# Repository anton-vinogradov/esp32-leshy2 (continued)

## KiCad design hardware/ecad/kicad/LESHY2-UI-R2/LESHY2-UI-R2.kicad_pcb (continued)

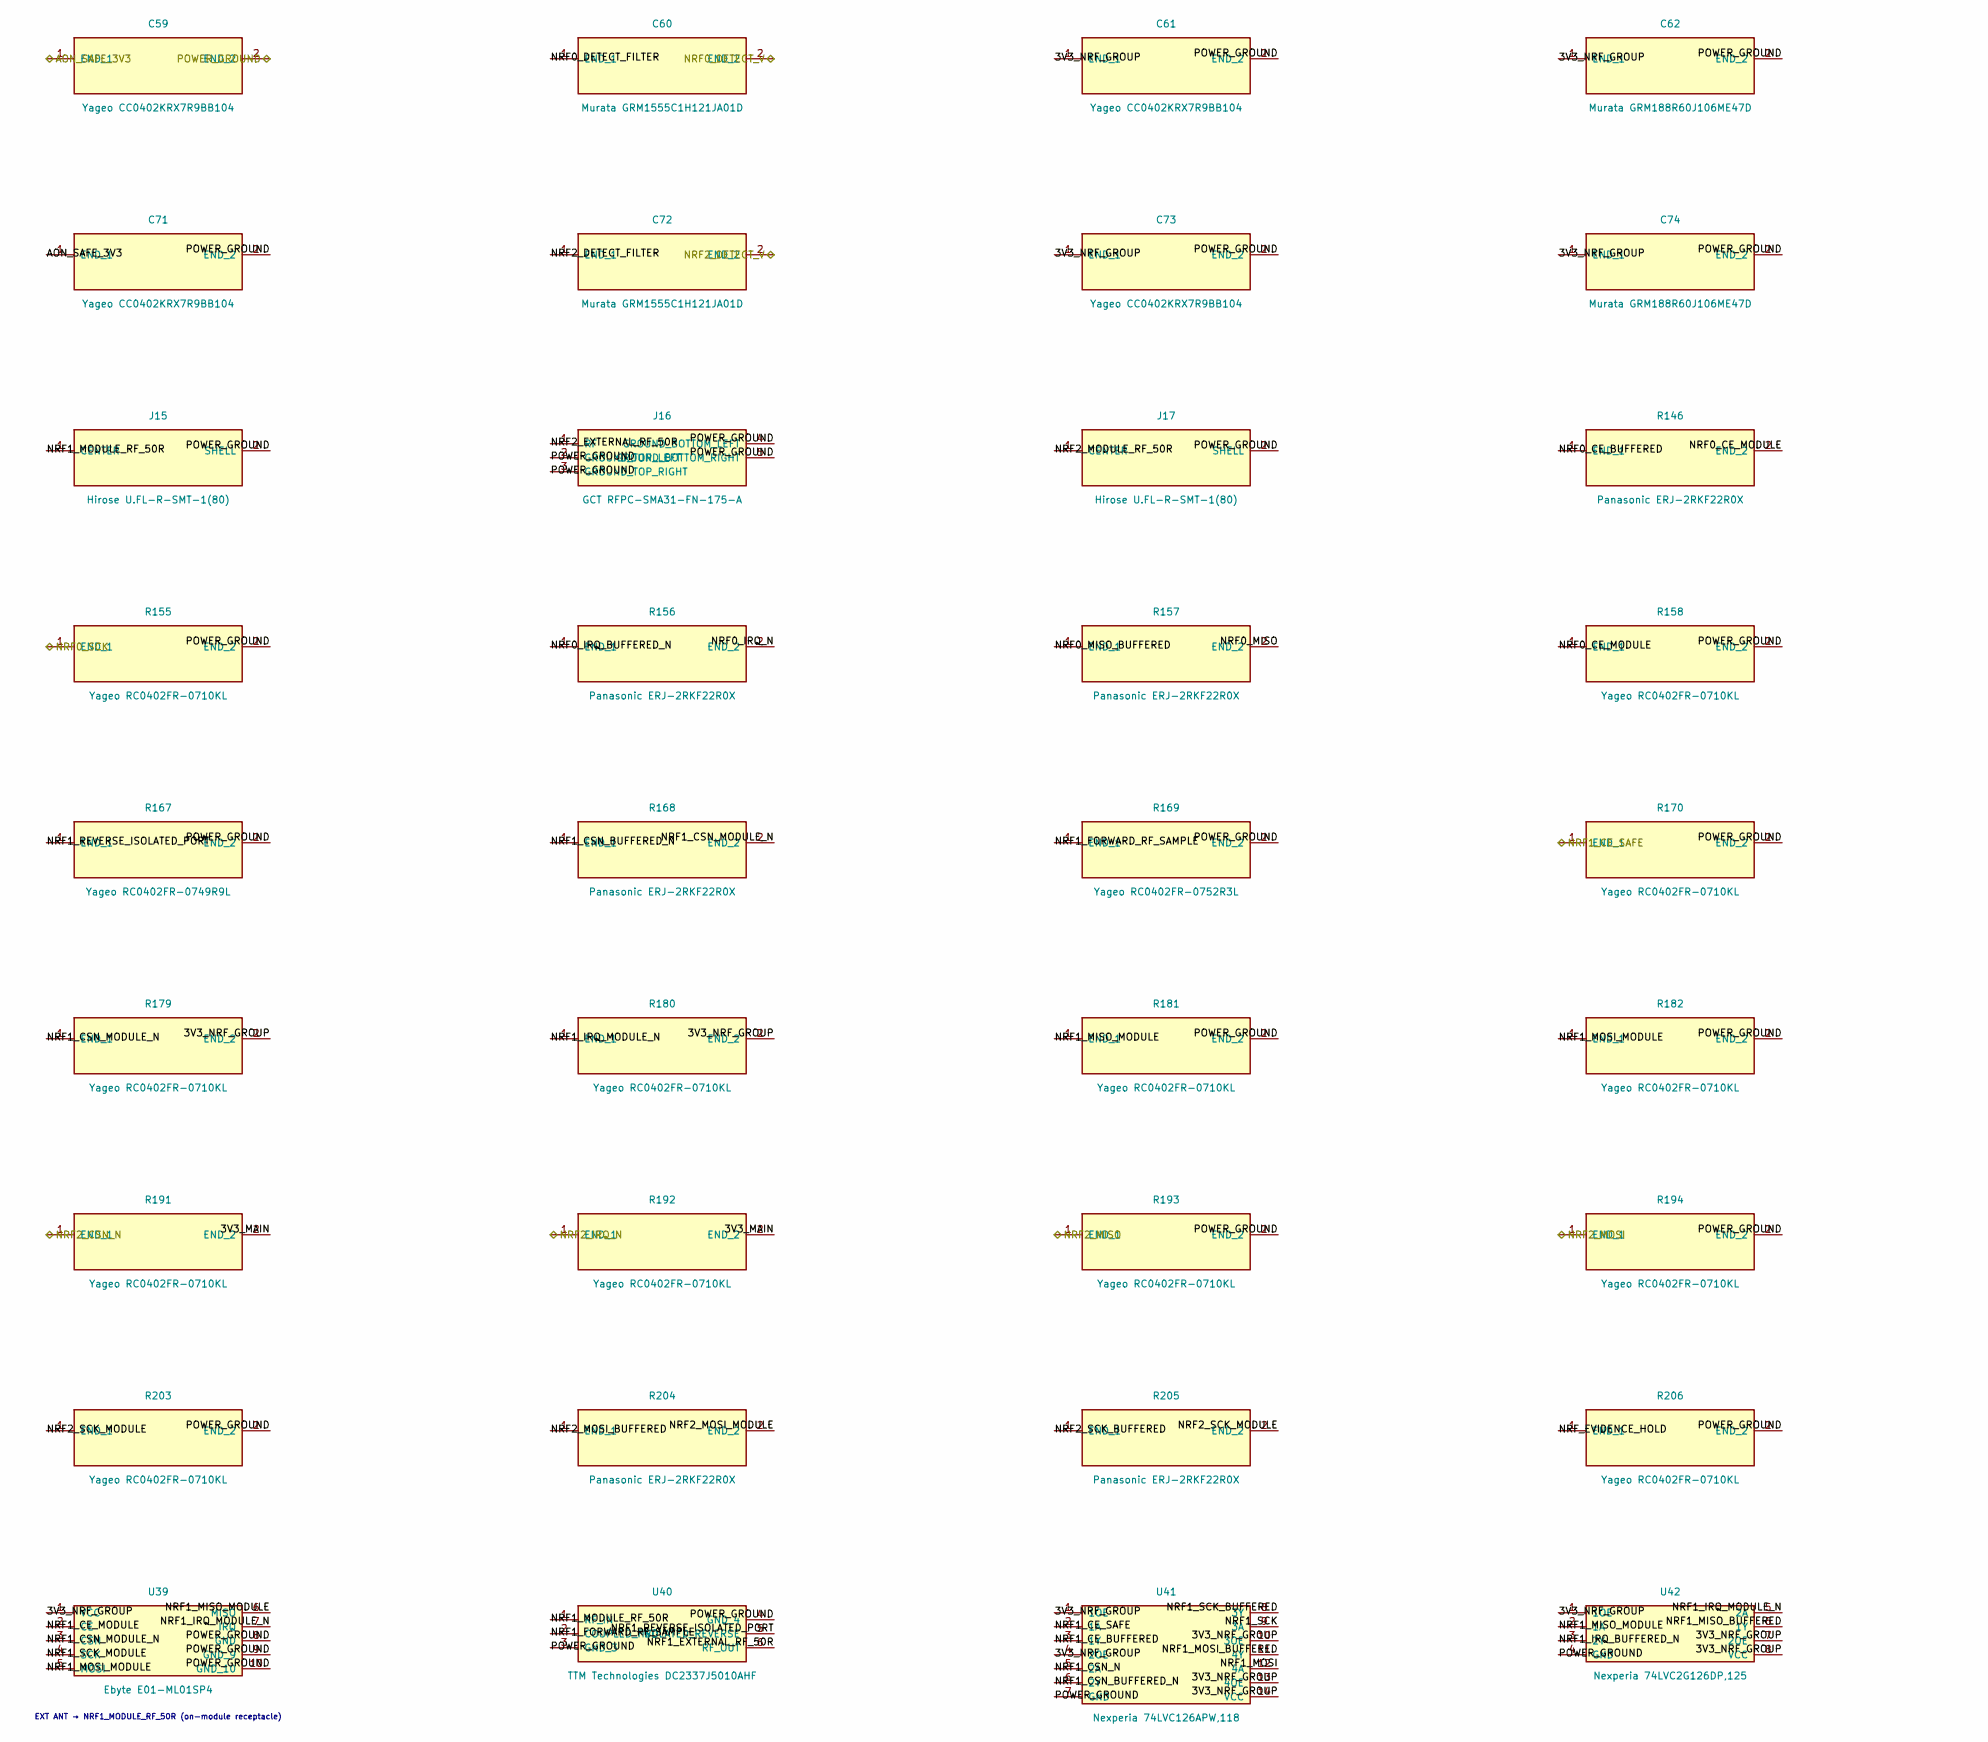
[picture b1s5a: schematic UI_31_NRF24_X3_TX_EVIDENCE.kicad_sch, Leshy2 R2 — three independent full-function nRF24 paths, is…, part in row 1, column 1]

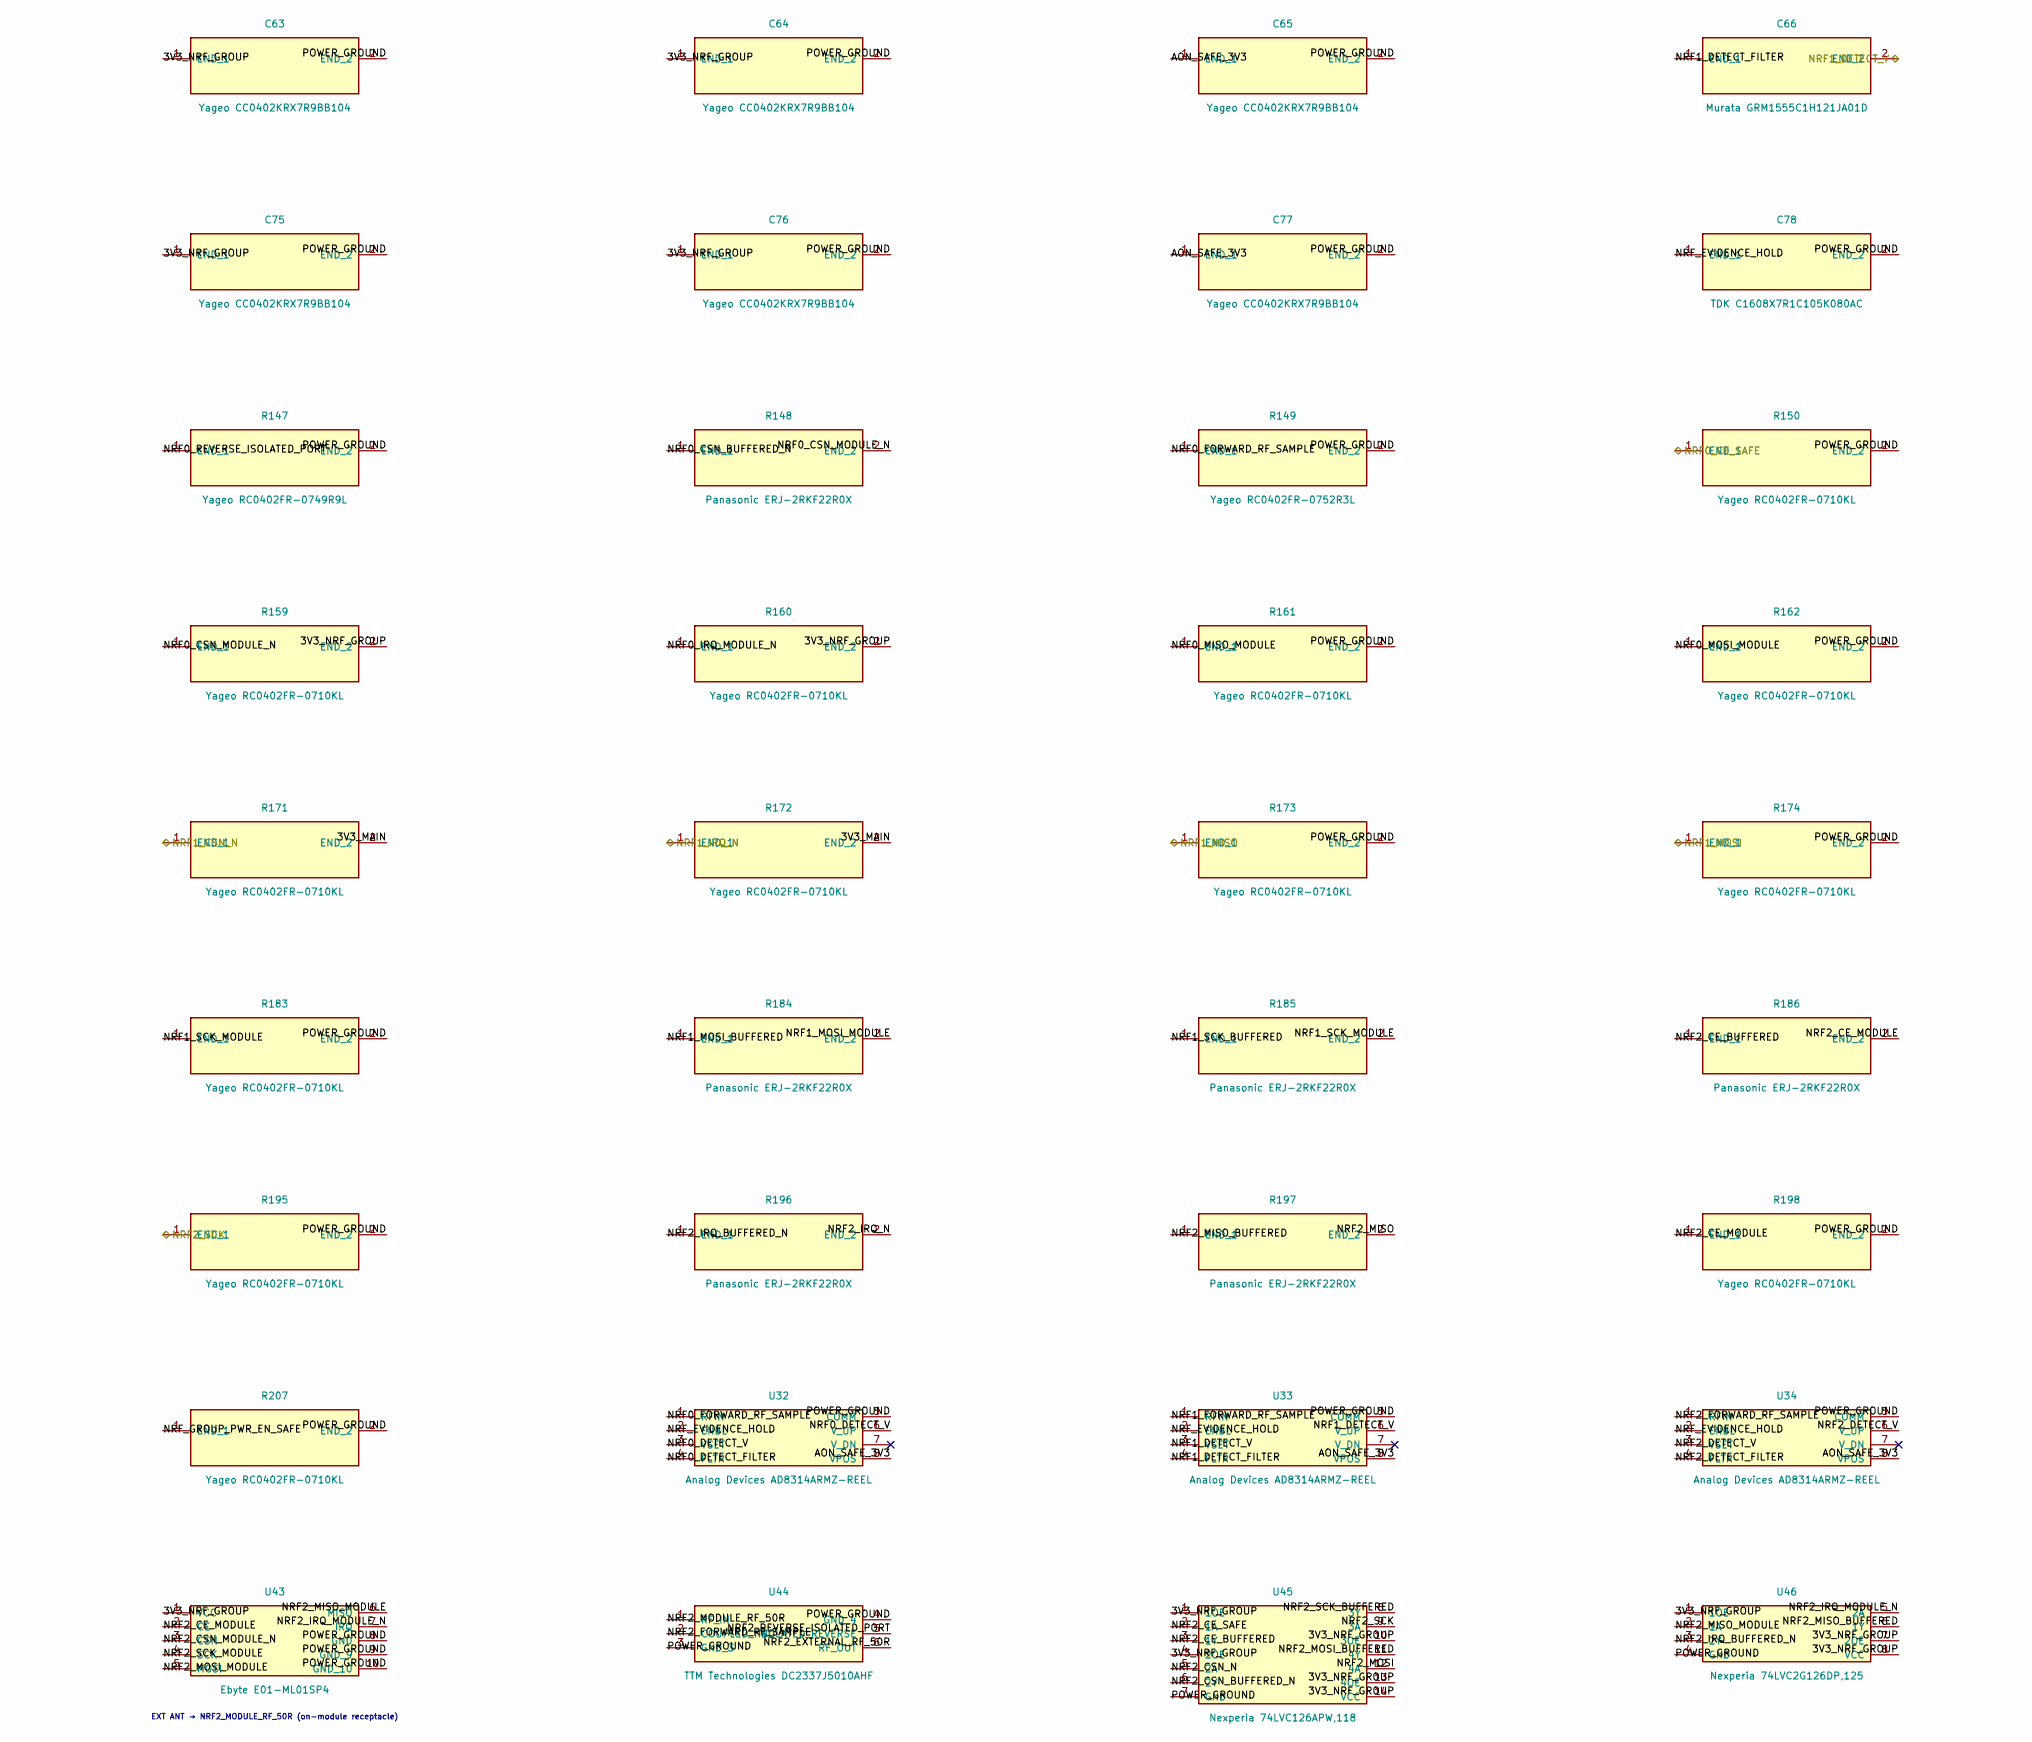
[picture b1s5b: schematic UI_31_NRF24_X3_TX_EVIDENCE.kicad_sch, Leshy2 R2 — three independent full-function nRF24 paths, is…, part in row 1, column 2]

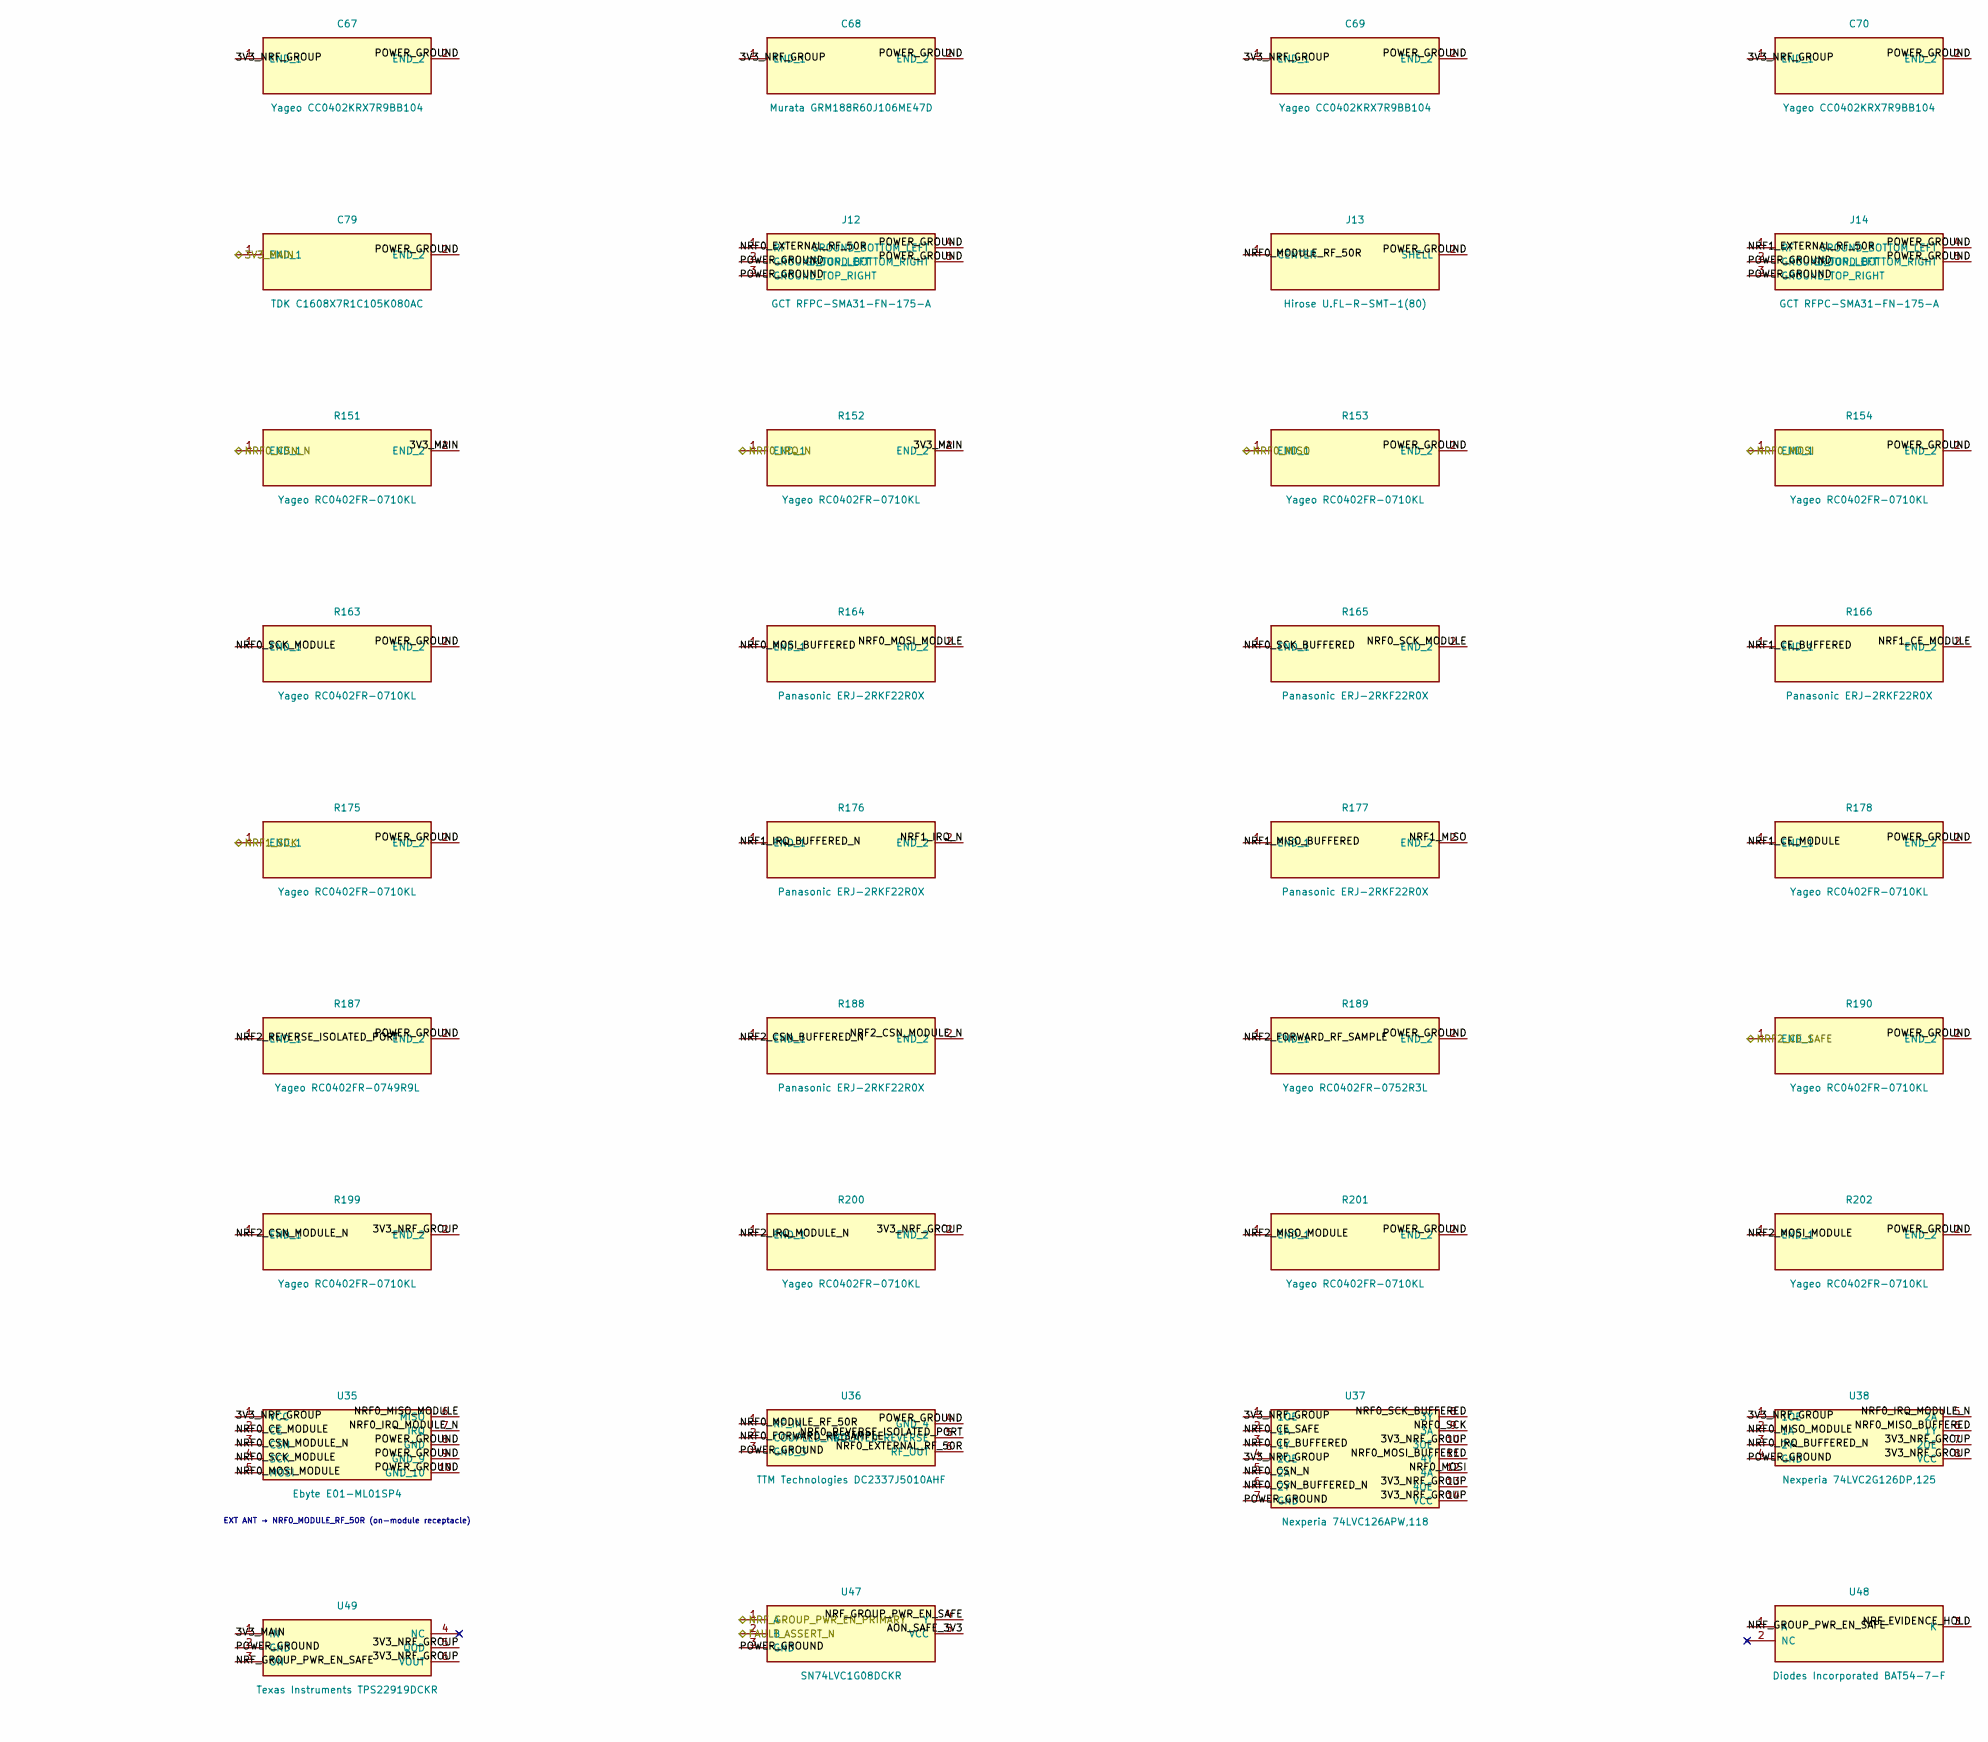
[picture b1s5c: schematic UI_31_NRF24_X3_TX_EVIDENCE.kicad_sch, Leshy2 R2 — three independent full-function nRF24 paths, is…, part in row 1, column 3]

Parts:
C59, C61, C63, C64, C65, C67, C69, C70, C71, C73, C75, C76, C77: Yageo CC0402KRX7R9BB104; C_0402_1005Metric
C60, C66, C72: Murata GRM1555C1H121JA01D; C_0402_1005Metric
C62, C68, C74: Murata GRM188R60J106ME47D; C_0603_1608Metric
C78, C79: TDK C1608X7R1C105K080AC; C_0603_1608Metric
J12, J14, J16: GCT RFPC-SMA31-FN-175-A; RFPC-SMA31-FN-175-A
J13, J15, J17: Hirose U.FL-R-SMT-1(80); U.FL_Hirose_U.FL-R-SMT-1_Vertical
R146, R148, R156, R157, R164, R165, R166, R168, R176, R177, R184, R185, R186, R188, R196, R197, R204, R205: Panasonic ERJ-2RKF22R0X; R_0402_1005Metric
R147, R167, R187: Yageo RC0402FR-0749R9L; R_0402_1005Metric
R149, R169, R189: Yageo RC0402FR-0752R3L; R_0402_1005Metric
R150, R151, R152, R153, R154, R155, R158, R159, R160, R161, R162, R163, R170, R171, R172, R173, R174, R175, R178, R179, R180, R181, R182, R183, R190, R191, R192, R193, R194, R195, R198, R199, R200, R201, R202, R203, R206, R207: Yageo RC0402FR-0710KL; R_0402_1005Metric
U32, U33, U34: Analog Devices AD8314ARMZ-REEL; MSOP-8_3x3mm_P0.65mm
U35, U39, U43: Ebyte E01-ML01SP4; Ebyte-E01-ML01SP4
U36, U40, U44: TTM Technologies DC2337J5010AHF; DC2337J5010AHF
U37, U41, U45: Nexperia 74LVC126APW,118; TSSOP-14_4.4x5mm_P0.65mm
U38, U42, U46: Nexperia 74LVC2G126DP,125; TSSOP-8_3x3mm_P0.65mm
U47: SN74LVC1G08DCKR; Texas_R-PDSO-G5_DCK-5
U48: Diodes Incorporated BAT54-7-F; SOT-23
U49: Texas Instruments TPS22919DCKR; SOT-363_SC-70-6

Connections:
/UI_10_S3_DISPLAY_TOUCH/3V3_MAIN: C79.1 (END_1), R151.2 (END_2), R152.2 (END_2), R171.2 (END_2), R172.2 (END_2), R191.2 (END_2), R192.2 (END_2), U49.1 (IN); also elsewhere on the board
/UI_10_S3_DISPLAY_TOUCH/AON_SAFE_3V3: C59.1 (END_1), C65.1 (END_1), C71.1 (END_1), C77.1 (END_1), U32.8 (VPOS), U33.8 (VPOS), U34.8 (VPOS), U47.5 (VCC); also elsewhere on the board
/UI_10_S3_DISPLAY_TOUCH/POWER_GROUND: C59.2 (END_2), C61.2 (END_2), C62.2 (END_2), C63.2 (END_2), C64.2 (END_2), C65.2 (END_2), C67.2 (END_2), C68.2 (END_2), C69.2 (END_2), C70.2 (END_2), C71.2 (END_2), C73.2 (END_2), C74.2 (END_2), C75.2 (END_2), C76.2 (END_2), C77.2 (END_2), C78.2 (END_2), C79.2 (END_2), J12.2 (GROUND_TOP_LEFT), J12.3 (GROUND_TOP_RIGHT), J12.4 (GROUND_BOTTOM_LEFT), J12.5 (GROUND_BOTTOM_RIGHT), J13.2 (SHELL), J14.2 (GROUND_TOP_LEFT), J14.3 (GROUND_TOP_RIGHT), J14.4 (GROUND_BOTTOM_LEFT), J14.5 (GROUND_BOTTOM_RIGHT), J15.2 (SHELL), J16.2 (GROUND_TOP_LEFT), J16.3 (GROUND_TOP_RIGHT), J16.4 (GROUND_BOTTOM_LEFT), J16.5 (GROUND_BOTTOM_RIGHT), J17.2 (SHELL), R147.2 (END_2), R149.2 (END_2), R150.2 (END_2), R153.2 (END_2), R154.2 (END_2), R155.2 (END_2), R158.2 (END_2), R161.2 (END_2), R162.2 (END_2), R163.2 (END_2), R167.2 (END_2), R169.2 (END_2), R170.2 (END_2), R173.2 (END_2), R174.2 (END_2), R175.2 (END_2), R178.2 (END_2), R181.2 (END_2), R182.2 (END_2), R183.2 (END_2), R187.2 (END_2), R189.2 (END_2), R190.2 (END_2), R193.2 (END_2), R194.2 (END_2), R195.2 (END_2), R198.2 (END_2), R201.2 (END_2), R202.2 (END_2), R203.2 (END_2), R206.2 (END_2), R207.2 (END_2), U32.5 (COMM), U33.5 (COMM), U34.5 (COMM), U35.8 (GND), U35.9 (GND_9), U35.10 (GND_10), U36.3 (GND_3), U36.4 (GND_4), U37.7 (GND), U38.4 (GND), U39.8 (GND), U39.9 (GND_9), U39.10 (GND_10), U40.3 (GND_3), U40.4 (GND_4), U41.7 (GND), U42.4 (GND), U43.8 (GND), U43.9 (GND_9), U43.10 (GND_10), U44.3 (GND_3), U44.4 (GND_4), U45.7 (GND), U46.4 (GND), U47.3 (GND), U49.2 (GND); also elsewhere on the board
/UI_20_C5_WIFI_IR_SERVICE/FAULT_ASSERT_N: U47.2 (B); also elsewhere on the board
/UI_31_NRF24_X3_TX_EVIDENCE/3V3_NRF_GROUP: C61.1 (END_1), C62.1 (END_1), C63.1 (END_1), C64.1 (END_1), C67.1 (END_1), C68.1 (END_1), C69.1 (END_1), C70.1 (END_1), C73.1 (END_1), C74.1 (END_1), C75.1 (END_1), C76.1 (END_1), R159.2 (END_2), R160.2 (END_2), R179.2 (END_2), R180.2 (END_2), R199.2 (END_2), R200.2 (END_2), U35.1 (VCC), U37.1 (1OE), U37.4 (2OE), U37.10 (3OE), U37.13 (4OE), U37.14 (VCC), U38.1 (1OE), U38.7 (2OE), U38.8 (VCC), U39.1 (VCC), U41.1 (1OE), U41.4 (2OE), U41.10 (3OE), U41.13 (4OE), U41.14 (VCC), U42.1 (1OE), U42.7 (2OE), U42.8 (VCC), U43.1 (VCC), U45.1 (1OE), U45.4 (2OE), U45.10 (3OE), U45.13 (4OE), U45.14 (VCC), U46.1 (1OE), U46.7 (2OE), U46.8 (VCC), U49.5 (QOD), U49.6 (VOUT)
/UI_31_NRF24_X3_TX_EVIDENCE/NRF0_CE_BUFFERED: R146.1 (END_1), U37.3 (1Y)
/UI_31_NRF24_X3_TX_EVIDENCE/NRF0_CE_MODULE: R146.2 (END_2), R158.1 (END_1), U35.2 (CE)
/UI_31_NRF24_X3_TX_EVIDENCE/NRF0_CE_SAFE: R150.1 (END_1), U37.2 (1A); also elsewhere on the board
/UI_31_NRF24_X3_TX_EVIDENCE/NRF0_CSN_BUFFERED_N: R148.1 (END_1), U37.6 (2Y)
/UI_31_NRF24_X3_TX_EVIDENCE/NRF0_CSN_MODULE_N: R148.2 (END_2), R159.1 (END_1), U35.3 (CSN)
/UI_31_NRF24_X3_TX_EVIDENCE/NRF0_CSN_N: R151.1 (END_1), U37.5 (2A); also elsewhere on the board
/UI_31_NRF24_X3_TX_EVIDENCE/NRF0_DETECT_FILTER: C60.1 (END_1), U32.4 (FLTR)
/UI_31_NRF24_X3_TX_EVIDENCE/NRF0_DETECT_V: C60.2 (END_2), U32.3 (VSET), U32.6 (V_UP); also elsewhere on the board
/UI_31_NRF24_X3_TX_EVIDENCE/NRF0_EXTERNAL_RF_50R: J12.1 (RF), U36.6 (RF_OUT)
/UI_31_NRF24_X3_TX_EVIDENCE/NRF0_FORWARD_RF_SAMPLE: R149.1 (END_1), U32.1 (RFIN), U36.2 (COUPLED_FWD)
/UI_31_NRF24_X3_TX_EVIDENCE/NRF0_IRQ_BUFFERED_N: R156.1 (END_1), U38.3 (2Y)
/UI_31_NRF24_X3_TX_EVIDENCE/NRF0_IRQ_MODULE_N: R160.1 (END_1), U35.7 (IRQ), U38.5 (2A)
/UI_31_NRF24_X3_TX_EVIDENCE/NRF0_IRQ_N: R152.1 (END_1), R156.2 (END_2); also elsewhere on the board
/UI_31_NRF24_X3_TX_EVIDENCE/NRF0_MISO: R153.1 (END_1), R157.2 (END_2); also elsewhere on the board
/UI_31_NRF24_X3_TX_EVIDENCE/NRF0_MISO_BUFFERED: R157.1 (END_1), U38.6 (1Y)
/UI_31_NRF24_X3_TX_EVIDENCE/NRF0_MISO_MODULE: R161.1 (END_1), U35.6 (MISO), U38.2 (1A)
/UI_31_NRF24_X3_TX_EVIDENCE/NRF0_MODULE_RF_50R: J13.1 (CENTER), U36.1 (RF_IN)
/UI_31_NRF24_X3_TX_EVIDENCE/NRF0_MOSI: R154.1 (END_1), U37.12 (4A); also elsewhere on the board
/UI_31_NRF24_X3_TX_EVIDENCE/NRF0_MOSI_BUFFERED: R164.1 (END_1), U37.11 (4Y)
/UI_31_NRF24_X3_TX_EVIDENCE/NRF0_MOSI_MODULE: R162.1 (END_1), R164.2 (END_2), U35.5 (MOSI)
/UI_31_NRF24_X3_TX_EVIDENCE/NRF0_REVERSE_ISOLATED_PORT: R147.1 (END_1), U36.5 (ISOLATED_REVERSE)
/UI_31_NRF24_X3_TX_EVIDENCE/NRF0_SCK: R155.1 (END_1), U37.9 (3A); also elsewhere on the board
/UI_31_NRF24_X3_TX_EVIDENCE/NRF0_SCK_BUFFERED: R165.1 (END_1), U37.8 (3Y)
/UI_31_NRF24_X3_TX_EVIDENCE/NRF0_SCK_MODULE: R163.1 (END_1), R165.2 (END_2), U35.4 (SCK)
/UI_31_NRF24_X3_TX_EVIDENCE/NRF1_CE_BUFFERED: R166.1 (END_1), U41.3 (1Y)
/UI_31_NRF24_X3_TX_EVIDENCE/NRF1_CE_MODULE: R166.2 (END_2), R178.1 (END_1), U39.2 (CE)
/UI_31_NRF24_X3_TX_EVIDENCE/NRF1_CE_SAFE: R170.1 (END_1), U41.2 (1A); also elsewhere on the board
/UI_31_NRF24_X3_TX_EVIDENCE/NRF1_CSN_BUFFERED_N: R168.1 (END_1), U41.6 (2Y)
/UI_31_NRF24_X3_TX_EVIDENCE/NRF1_CSN_MODULE_N: R168.2 (END_2), R179.1 (END_1), U39.3 (CSN)
/UI_31_NRF24_X3_TX_EVIDENCE/NRF1_CSN_N: R171.1 (END_1), U41.5 (2A); also elsewhere on the board
/UI_31_NRF24_X3_TX_EVIDENCE/NRF1_DETECT_FILTER: C66.1 (END_1), U33.4 (FLTR)
/UI_31_NRF24_X3_TX_EVIDENCE/NRF1_DETECT_V: C66.2 (END_2), U33.3 (VSET), U33.6 (V_UP); also elsewhere on the board
/UI_31_NRF24_X3_TX_EVIDENCE/NRF1_EXTERNAL_RF_50R: J14.1 (RF), U40.6 (RF_OUT)
/UI_31_NRF24_X3_TX_EVIDENCE/NRF1_FORWARD_RF_SAMPLE: R169.1 (END_1), U33.1 (RFIN), U40.2 (COUPLED_FWD)
/UI_31_NRF24_X3_TX_EVIDENCE/NRF1_IRQ_BUFFERED_N: R176.1 (END_1), U42.3 (2Y)
/UI_31_NRF24_X3_TX_EVIDENCE/NRF1_IRQ_MODULE_N: R180.1 (END_1), U39.7 (IRQ), U42.5 (2A)
/UI_31_NRF24_X3_TX_EVIDENCE/NRF1_IRQ_N: R172.1 (END_1), R176.2 (END_2); also elsewhere on the board
/UI_31_NRF24_X3_TX_EVIDENCE/NRF1_MISO: R173.1 (END_1), R177.2 (END_2); also elsewhere on the board
/UI_31_NRF24_X3_TX_EVIDENCE/NRF1_MISO_BUFFERED: R177.1 (END_1), U42.6 (1Y)
/UI_31_NRF24_X3_TX_EVIDENCE/NRF1_MISO_MODULE: R181.1 (END_1), U39.6 (MISO), U42.2 (1A)
/UI_31_NRF24_X3_TX_EVIDENCE/NRF1_MODULE_RF_50R: J15.1 (CENTER), U40.1 (RF_IN)
/UI_31_NRF24_X3_TX_EVIDENCE/NRF1_MOSI: R174.1 (END_1), U41.12 (4A); also elsewhere on the board
/UI_31_NRF24_X3_TX_EVIDENCE/NRF1_MOSI_BUFFERED: R184.1 (END_1), U41.11 (4Y)
/UI_31_NRF24_X3_TX_EVIDENCE/NRF1_MOSI_MODULE: R182.1 (END_1), R184.2 (END_2), U39.5 (MOSI)
/UI_31_NRF24_X3_TX_EVIDENCE/NRF1_REVERSE_ISOLATED_PORT: R167.1 (END_1), U40.5 (ISOLATED_REVERSE)
/UI_31_NRF24_X3_TX_EVIDENCE/NRF1_SCK: R175.1 (END_1), U41.9 (3A); also elsewhere on the board
/UI_31_NRF24_X3_TX_EVIDENCE/NRF1_SCK_BUFFERED: R185.1 (END_1), U41.8 (3Y)
/UI_31_NRF24_X3_TX_EVIDENCE/NRF1_SCK_MODULE: R183.1 (END_1), R185.2 (END_2), U39.4 (SCK)
/UI_31_NRF24_X3_TX_EVIDENCE/NRF2_CE_BUFFERED: R186.1 (END_1), U45.3 (1Y)
/UI_31_NRF24_X3_TX_EVIDENCE/NRF2_CE_MODULE: R186.2 (END_2), R198.1 (END_1), U43.2 (CE)
/UI_31_NRF24_X3_TX_EVIDENCE/NRF2_CE_SAFE: R190.1 (END_1), U45.2 (1A); also elsewhere on the board
/UI_31_NRF24_X3_TX_EVIDENCE/NRF2_CSN_BUFFERED_N: R188.1 (END_1), U45.6 (2Y)
/UI_31_NRF24_X3_TX_EVIDENCE/NRF2_CSN_MODULE_N: R188.2 (END_2), R199.1 (END_1), U43.3 (CSN)
/UI_31_NRF24_X3_TX_EVIDENCE/NRF2_CSN_N: R191.1 (END_1), U45.5 (2A); also elsewhere on the board
/UI_31_NRF24_X3_TX_EVIDENCE/NRF2_DETECT_FILTER: C72.1 (END_1), U34.4 (FLTR)
/UI_31_NRF24_X3_TX_EVIDENCE/NRF2_DETECT_V: C72.2 (END_2), U34.3 (VSET), U34.6 (V_UP); also elsewhere on the board
/UI_31_NRF24_X3_TX_EVIDENCE/NRF2_EXTERNAL_RF_50R: J16.1 (RF), U44.6 (RF_OUT)
/UI_31_NRF24_X3_TX_EVIDENCE/NRF2_FORWARD_RF_SAMPLE: R189.1 (END_1), U34.1 (RFIN), U44.2 (COUPLED_FWD)
/UI_31_NRF24_X3_TX_EVIDENCE/NRF2_IRQ_BUFFERED_N: R196.1 (END_1), U46.3 (2Y)
/UI_31_NRF24_X3_TX_EVIDENCE/NRF2_IRQ_MODULE_N: R200.1 (END_1), U43.7 (IRQ), U46.5 (2A)
/UI_31_NRF24_X3_TX_EVIDENCE/NRF2_IRQ_N: R192.1 (END_1), R196.2 (END_2); also elsewhere on the board
/UI_31_NRF24_X3_TX_EVIDENCE/NRF2_MISO: R193.1 (END_1), R197.2 (END_2); also elsewhere on the board
/UI_31_NRF24_X3_TX_EVIDENCE/NRF2_MISO_BUFFERED: R197.1 (END_1), U46.6 (1Y)
/UI_31_NRF24_X3_TX_EVIDENCE/NRF2_MISO_MODULE: R201.1 (END_1), U43.6 (MISO), U46.2 (1A)
/UI_31_NRF24_X3_TX_EVIDENCE/NRF2_MODULE_RF_50R: J17.1 (CENTER), U44.1 (RF_IN)
/UI_31_NRF24_X3_TX_EVIDENCE/NRF2_MOSI: R194.1 (END_1), U45.12 (4A); also elsewhere on the board
/UI_31_NRF24_X3_TX_EVIDENCE/NRF2_MOSI_BUFFERED: R204.1 (END_1), U45.11 (4Y)
/UI_31_NRF24_X3_TX_EVIDENCE/NRF2_MOSI_MODULE: R202.1 (END_1), R204.2 (END_2), U43.5 (MOSI)
/UI_31_NRF24_X3_TX_EVIDENCE/NRF2_REVERSE_ISOLATED_PORT: R187.1 (END_1), U44.5 (ISOLATED_REVERSE)
/UI_31_NRF24_X3_TX_EVIDENCE/NRF2_SCK: R195.1 (END_1), U45.9 (3A); also elsewhere on the board
/UI_31_NRF24_X3_TX_EVIDENCE/NRF2_SCK_BUFFERED: R205.1 (END_1), U45.8 (3Y)
/UI_31_NRF24_X3_TX_EVIDENCE/NRF2_SCK_MODULE: R203.1 (END_1), R205.2 (END_2), U43.4 (SCK)
/UI_31_NRF24_X3_TX_EVIDENCE/NRF_EVIDENCE_HOLD: C78.1 (END_1), R206.1 (END_1), U32.2 (ENBL), U33.2 (ENBL), U34.2 (ENBL), U48.3 (K)
/UI_31_NRF24_X3_TX_EVIDENCE/NRF_GROUP_PWR_EN_PRIMARY: U47.1 (A); also elsewhere on the board
/UI_31_NRF24_X3_TX_EVIDENCE/NRF_GROUP_PWR_EN_SAFE: R207.1 (END_1), U47.4 (Y), U48.1 (A), U49.3 (ON)

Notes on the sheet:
EXT ANT → NRF0_MODULE_RF_50R (on-module receptacle)
EXT ANT → NRF1_MODULE_RF_50R (on-module receptacle)
EXT ANT → NRF2_MODULE_RF_50R (on-module receptacle)

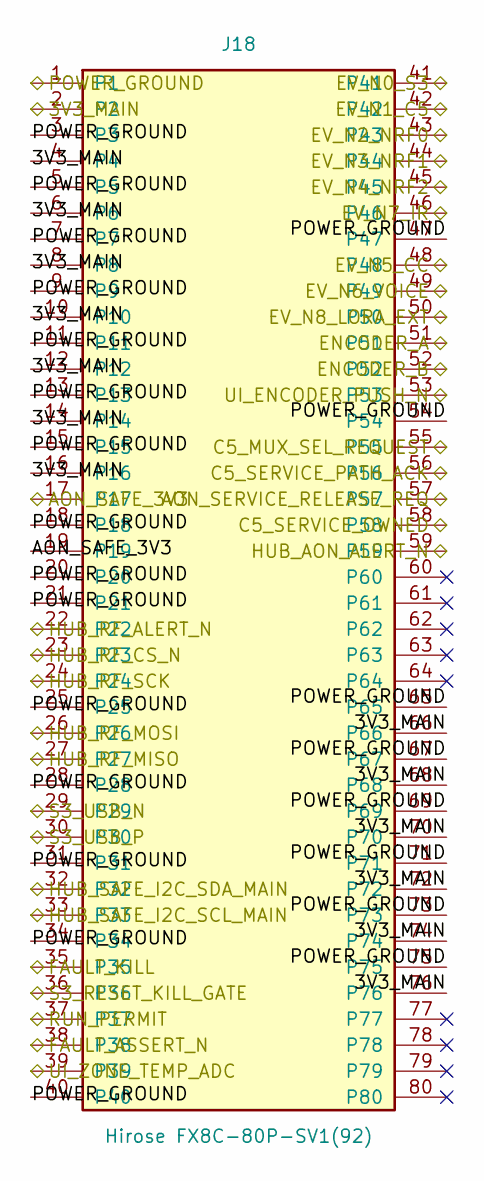
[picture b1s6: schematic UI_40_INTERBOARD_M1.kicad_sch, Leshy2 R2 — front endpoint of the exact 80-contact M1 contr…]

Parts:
J18: Hirose FX8C-80P-SV1(92); Hirose_FX8-80P-SV_2x40_P0.6mm

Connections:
/UI_10_S3_DISPLAY_TOUCH/3V3_MAIN: J18.2, J18.4, J18.6, J18.8, J18.10, J18.12, J18.14, J18.16, J18.66, J18.68, J18.70, J18.72, J18.74, J18.76; also elsewhere on the board
/UI_10_S3_DISPLAY_TOUCH/AON_SAFE_3V3: J18.17, J18.19; also elsewhere on the board
/UI_10_S3_DISPLAY_TOUCH/ENCODER_A: J18.51; also elsewhere on the board
/UI_10_S3_DISPLAY_TOUCH/ENCODER_B: J18.52; also elsewhere on the board
/UI_10_S3_DISPLAY_TOUCH/POWER_GROUND: J18.1, J18.3, J18.5, J18.7, J18.9, J18.11, J18.13, J18.15, J18.18, J18.20, J18.21, J18.25, J18.28, J18.31, J18.34, J18.40, J18.47, J18.54, J18.65, J18.67, J18.69, J18.71, J18.73, J18.75; also elsewhere on the board
/UI_10_S3_DISPLAY_TOUCH/S3_RESET_KILL_GATE: J18.36; also elsewhere on the board
/UI_10_S3_DISPLAY_TOUCH/S3_USB_N: J18.29; also elsewhere on the board
/UI_10_S3_DISPLAY_TOUCH/S3_USB_P: J18.30; also elsewhere on the board
/UI_11_STORAGE_CONTROLS_INDICATORS/EV_N5_CC: J18.48; also elsewhere on the board
/UI_11_STORAGE_CONTROLS_INDICATORS/EV_N6_VOICE: J18.49; also elsewhere on the board
/UI_11_STORAGE_CONTROLS_INDICATORS/EV_N8_LORA_EXT: J18.50; also elsewhere on the board
/UI_11_STORAGE_CONTROLS_INDICATORS/FAULT_KILL: J18.35; also elsewhere on the board
/UI_11_STORAGE_CONTROLS_INDICATORS/UI_ENCODER_PUSH_N: J18.53; also elsewhere on the board
/UI_11_STORAGE_CONTROLS_INDICATORS/UI_ZONE_TEMP_ADC: J18.39; also elsewhere on the board
/UI_20_C5_WIFI_IR_SERVICE/AON_SERVICE_RELEASE_REQ: J18.57; also elsewhere on the board
/UI_20_C5_WIFI_IR_SERVICE/C5_MUX_SEL_REQUEST: J18.55; also elsewhere on the board
/UI_20_C5_WIFI_IR_SERVICE/C5_SERVICE_OWNED: J18.58; also elsewhere on the board
/UI_20_C5_WIFI_IR_SERVICE/C5_SERVICE_PATH_ACK: J18.56; also elsewhere on the board
/UI_20_C5_WIFI_IR_SERVICE/EV_N1_C5: J18.42; also elsewhere on the board
/UI_20_C5_WIFI_IR_SERVICE/EV_N7_IR: J18.46; also elsewhere on the board
/UI_20_C5_WIFI_IR_SERVICE/FAULT_ASSERT_N: J18.38; also elsewhere on the board
/UI_20_C5_WIFI_IR_SERVICE/RUN_PERMIT: J18.37; also elsewhere on the board
/UI_30_HUB_RP_CORE_SERVICE/HUB_AON_ALERT_N: J18.59; also elsewhere on the board
/UI_30_HUB_RP_CORE_SERVICE/HUB_RF_ALERT_N: J18.22; also elsewhere on the board
/UI_30_HUB_RP_CORE_SERVICE/HUB_RF_CS_N: J18.23; also elsewhere on the board
/UI_30_HUB_RP_CORE_SERVICE/HUB_RF_MISO: J18.27; also elsewhere on the board
/UI_30_HUB_RP_CORE_SERVICE/HUB_RF_MOSI: J18.26; also elsewhere on the board
/UI_30_HUB_RP_CORE_SERVICE/HUB_RF_SCK: J18.24; also elsewhere on the board
/UI_30_HUB_RP_CORE_SERVICE/HUB_SAFE_I2C_SCL_MAIN: J18.33; also elsewhere on the board
/UI_30_HUB_RP_CORE_SERVICE/HUB_SAFE_I2C_SDA_MAIN: J18.32; also elsewhere on the board
/UI_50_FRONT_POWER_SAFETY/EV_N0_S3: J18.41; also elsewhere on the board
/UI_50_FRONT_POWER_SAFETY/EV_N2_NRF0: J18.43; also elsewhere on the board
/UI_50_FRONT_POWER_SAFETY/EV_N3_NRF1: J18.44; also elsewhere on the board
/UI_50_FRONT_POWER_SAFETY/EV_N4_NRF2: J18.45; also elsewhere on the board
